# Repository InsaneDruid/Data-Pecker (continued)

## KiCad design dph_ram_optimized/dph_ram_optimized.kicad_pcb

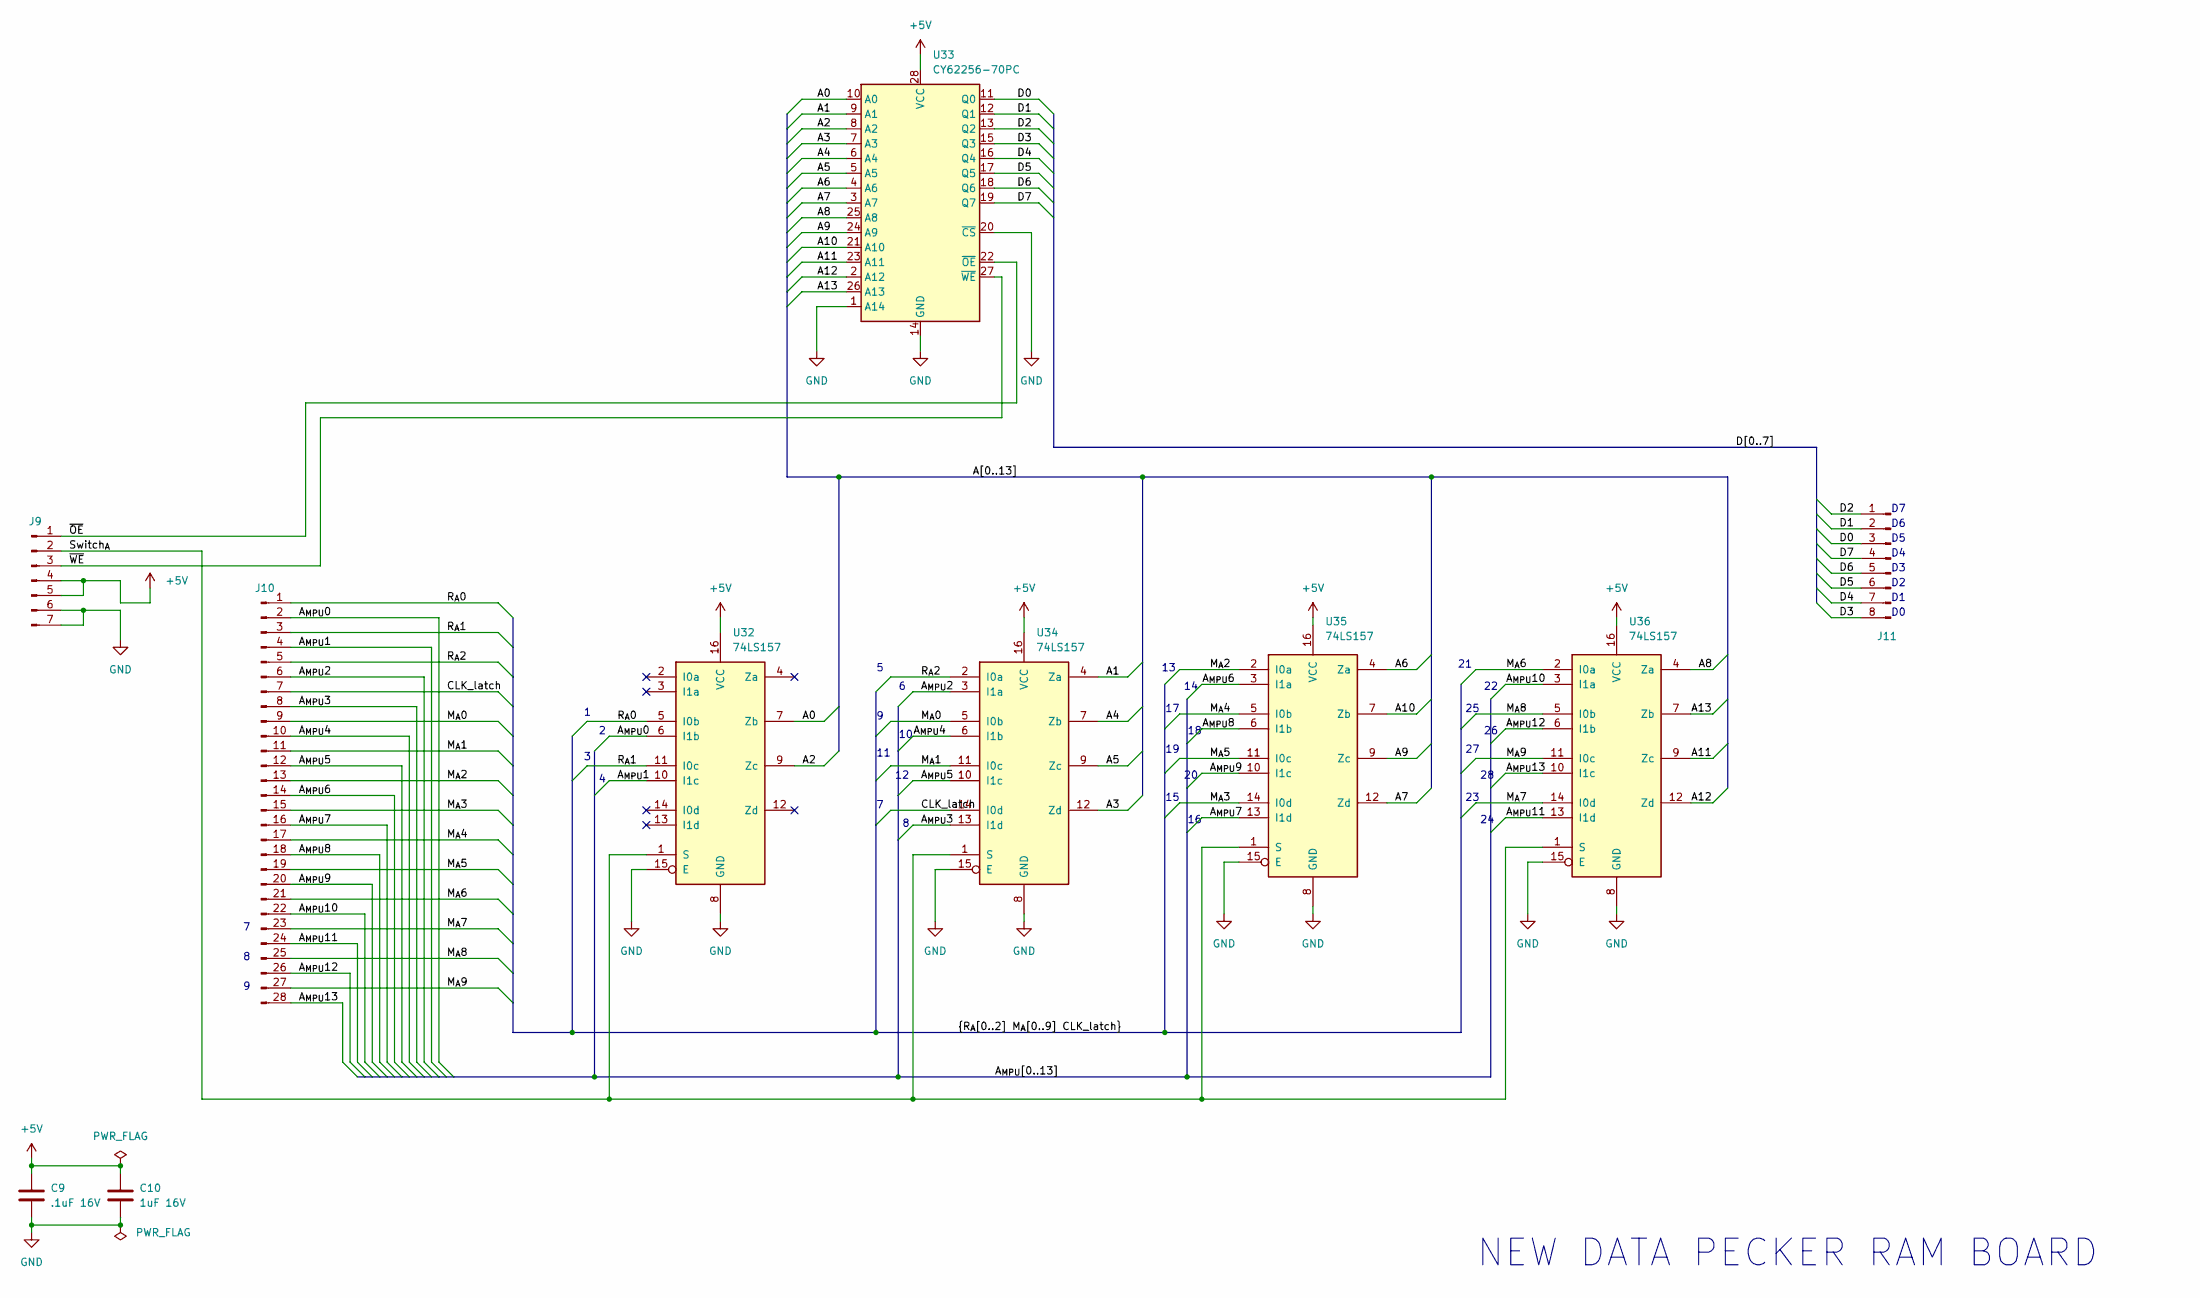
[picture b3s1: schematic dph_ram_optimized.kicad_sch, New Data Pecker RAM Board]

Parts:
C9: .1uF 16V; C_Disc_D4.3mm_W1.9mm_P5.08mm
C10: 1uF 16V; C_Disc_D3.0mm_W1.6mm_P2.50mm
J9: Conn_01x07_Pin; PinHeader_1x07_P2.54mm_Vertical
J10: Conn_01x28_Pin; PinHeader_1x28_P2.54mm_Vertical
J11: Conn_01x08_Pin; PinHeader_1x08_P2.54mm_Vertical
U32, U34, U35, U36: 74LS157; DIP-16_W7.62mm_LongPads
U33: CY62256-70PC; DIP-28_W15.24mm_LongPads

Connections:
+5V: C9.1, C10.1, J9.4, J9.5, U32.16 (VCC), U33.28 (VCC), U34.16 (VCC), U35.16 (VCC), U36.16 (VCC)
/A0: U32.7 (Zb), U33.10 (A0)
/A1: U33.9 (A1), U34.4 (Za)
/A2: U32.9 (Zc), U33.8 (A2)
/A3: U33.7 (A3), U34.12 (Zd)
/A4: U33.6 (A4), U34.7 (Zb)
/A5: U33.5 (A5), U34.9 (Zc)
/A6: U33.4 (A6), U35.4 (Za)
/A7: U33.3 (A7), U35.12 (Zd)
/A8: U33.25 (A8), U36.4 (Za)
/A9: U33.24 (A9), U35.9 (Zc)
/A10: U33.21 (A10), U35.7 (Zb)
/A11: U33.23 (A11), U36.9 (Zc)
/A12: U33.2 (A12), U36.12 (Zd)
/A13: U33.26 (A13), U36.7 (Zb)
/A_{MPU}0: J10.2, U32.6 (I1b)
/A_{MPU}1: J10.4, U32.10 (I1c)
/A_{MPU}2: J10.6, U34.3 (I1a)
/A_{MPU}3: J10.8, U34.13 (I1d)
/A_{MPU}4: J10.10, U34.6 (I1b)
/A_{MPU}5: J10.12, U34.10 (I1c)
/A_{MPU}6: J10.14, U35.3 (I1a)
/A_{MPU}7: J10.16, U35.13 (I1d)
/A_{MPU}8: J10.18, U35.6 (I1b)
/A_{MPU}9: J10.20, U35.10 (I1c)
/A_{MPU}10: J10.22, U36.3 (I1a)
/A_{MPU}11: J10.24, U36.13 (I1d)
/A_{MPU}12: J10.26, U36.6 (I1b)
/A_{MPU}13: J10.28, U36.10 (I1c)
/CLK_latch: J10.7, U34.14 (I0d)
/D0: J11.3, U33.11 (Q0)
/D1: J11.2, U33.12 (Q1)
/D2: J11.1, U33.13 (Q2)
/D3: J11.8, U33.15 (Q3)
/D4: J11.7, U33.16 (Q4)
/D5: J11.6, U33.17 (Q5)
/D6: J11.5, U33.18 (Q6)
/D7: J11.4, U33.19 (Q7)
/M_{A}0: J10.9, U34.5 (I0b)
/M_{A}1: J10.11, U34.11 (I0c)
/M_{A}2: J10.13, U35.2 (I0a)
/M_{A}3: J10.15, U35.14 (I0d)
/M_{A}4: J10.17, U35.5 (I0b)
/M_{A}5: J10.19, U35.11 (I0c)
/M_{A}6: J10.21, U36.2 (I0a)
/M_{A}7: J10.23, U36.14 (I0d)
/M_{A}8: J10.25, U36.5 (I0b)
/M_{A}9: J10.27, U36.11 (I0c)
/R_{A}0: J10.1, U32.5 (I0b)
/R_{A}1: J10.3, U32.11 (I0c)
/R_{A}2: J10.5, U34.2 (I0a)
/Switch_{A}: J9.2, U32.1 (S), U34.1 (S), U35.1 (S), U36.1 (S)
/~OE: J9.1, U33.22 (~OE)
/~WE: J9.3, U33.27 (~WE)
GND: C9.2, C10.2, J9.6, J9.7, U32.8 (GND), U32.15 (E), U33.1 (A14), U33.14 (GND), U33.20 (~CS), U34.8 (GND), U34.15 (E), U35.8 (GND), U35.15 (E), U36.8 (GND), U36.15 (E)

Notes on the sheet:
NEW DATA PECKER RAM BOARD

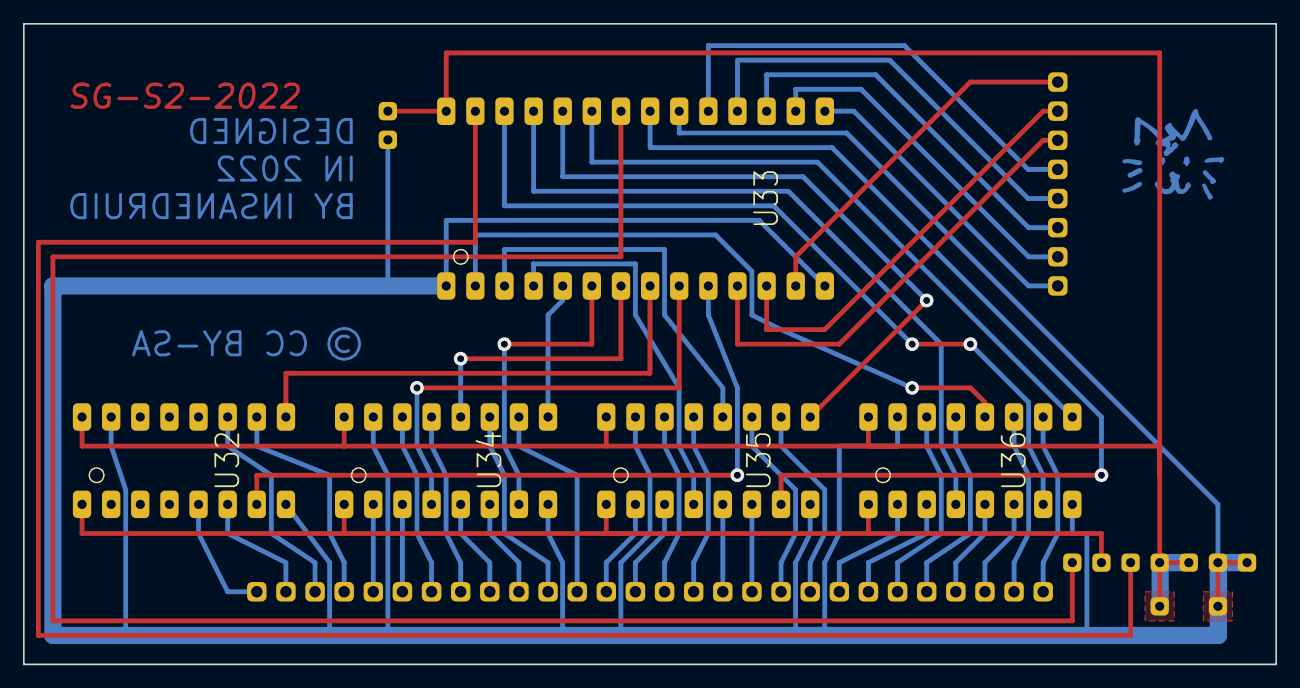
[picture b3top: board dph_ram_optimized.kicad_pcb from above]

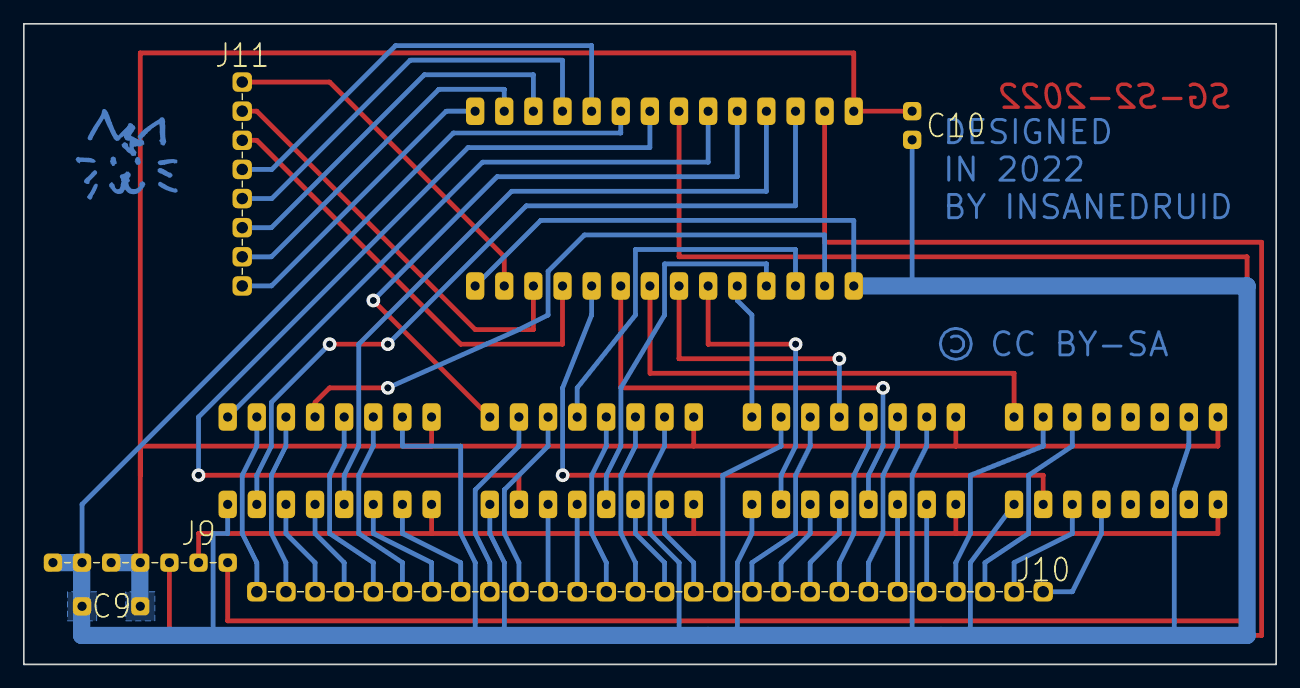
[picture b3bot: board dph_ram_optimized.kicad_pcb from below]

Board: 2 copper layers, 109.2 x 55.9 mm, 10 parts (3 on the bottom side), 55 nets.

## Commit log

2024-02-16 kicad drawing sheet fixes
    fixed license links in drawing sheets to match board prints, readme and project
2024-02-26 fixed description for external wiring
    fixed and added UD3 Pin information for 8032030 and 8032090 boards
